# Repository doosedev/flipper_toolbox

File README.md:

<!-- Improved compatibility of back to top link: See: https://github.com/othneildrew/Best-README-Template/pull/73 -->

<!--
*** Thanks for checking out the Best-README-Template. If you have a suggestion
*** that would make this better, please fork the repo and create a pull request
*** or simply open an issue with the tag "enhancement".
*** Don't forget to give the project a star!
*** Thanks again! Now go create something AMAZING! :D
-->

<!-- PROJECT SHIELDS -->
<!--
*** I'm using markdown "reference style" links for readability.
*** Reference links are enclosed in brackets [ ] instead of parentheses ( ).
*** See the bottom of this document for the declaration of the reference variables
*** for contributors-url, forks-url, etc. This is an optional, concise syntax you may use.
*** https://www.markdownguide.org/basic-syntax/#reference-style-links
-->

<!-- PROJECT LOGO -->
<div align="center">
  <a href="https://github.com/doosedev/flipper_toolbox">
    <picture>
      <source media="(prefers-color-scheme: dark)" srcset="/.github/assets/banner_dark.png">
      <source media="(prefers-color-scheme: light)" srcset="/.github/assets/banner_light.png">
      
    </picture>
  </a>

  <br/>

  [![Contributors][contributors-shield]][contributors-url]
  [![Forks][forks-shield]][forks-url]
  [![Stargazers][stars-shield]][stars-url]<br/>
  [![Issues][issues-shield]][issues-url]
  [![MIT License][license-shield]][license-url]
  [![LinkedIn][linkedin-shield]][linkedin-url]

  <h3 align="center">Flipper Toolbox</h3>

  <p align="center">
    A collection of useful expansion boards for Flipper Zero
    <br/>
    <a href="https://github.com/doosedev/flipper_toolbox/issues">Report Bug</a>
    ·
    <a href="https://github.com/doosedev/flipper_toolbox/issues">Request Feature</a>
  </p>
</div>

<!-- MARKDOWN LINKS & IMAGES -->
<!-- https://www.markdownguide.org/basic-syntax/#reference-style-links -->
[contributors-shield]: https://img.shields.io/github/contributors/doosedev/flipper_toolbox.svg?style=for-the-badge
[contributors-url]: https://github.com/doosedev/flipper_toolbox/graphs/contributors
[forks-shield]: https://img.shields.io/github/forks/doosedev/flipper_toolbox.svg?style=for-the-badge
[forks-url]: https://github.com/doosedev/flipper_toolbox/network/members
[stars-shield]: https://img.shields.io/github/stars/doosedev/flipper_toolbox.svg?style=for-the-badge
[stars-url]: https://github.com/doosedev/flipper_toolbox/stargazers
[issues-shield]: https://img.shields.io/github/issues/doosedev/flipper_toolbox.svg?style=for-the-badge
[issues-url]: https://github.com/doosedev/flipper_toolbox/issues
[license-shield]: https://img.shields.io/github/license/doosedev/flipper_toolbox.svg?style=for-the-badge
[license-url]: https://github.com/doosedev/flipper_toolbox/blob/master/LICENSE.txt
[linkedin-shield]: https://img.shields.io/badge/-LinkedIn-black.svg?style=for-the-badge&logo=linkedin&colorB=555
[linkedin-url]: https://linkedin.com/in/jordan-doose-381bb4161

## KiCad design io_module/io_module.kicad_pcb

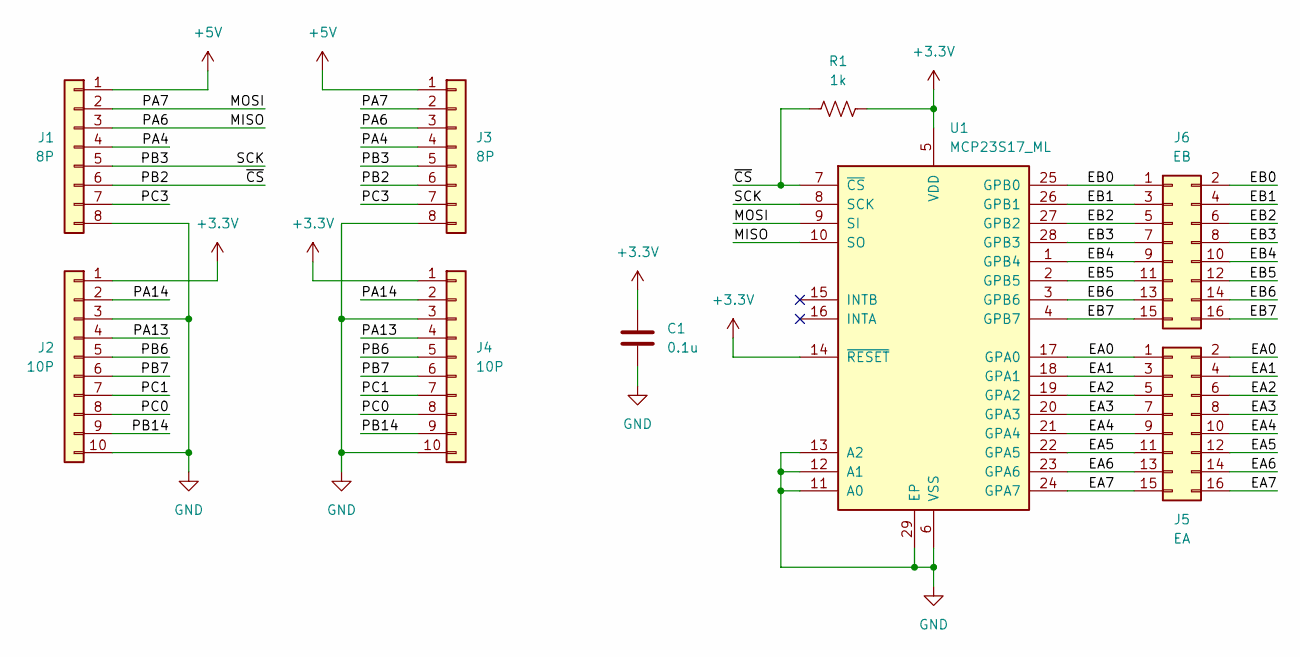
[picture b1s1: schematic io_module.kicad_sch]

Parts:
C1: 0.1u; C_0603_1608Metric_Pad1.08x0.95mm_HandSolder
J1: 8P; PinHeader_1x08_P2.54mm_Horizontal
J2: 10P; PinHeader_1x10_P2.54mm_Horizontal
J3: 8P; PinHeader_1x08_P2.54mm_Vertical
J4: 10P; PinHeader_1x10_P2.54mm_Vertical
J5: EA; PinHeader_2x08_P2.54mm_Vertical
J6: EB; PinHeader_2x08_P2.54mm_Vertical
R1: 1k; R_0603_1608Metric_Pad0.98x0.95mm_HandSolder
U1: MCP23S17_ML; QFN-28-1EP_6x6mm_P0.65mm_EP4.25x4.25mm

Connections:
+3.3V: C1.1, J2.1, J4.1, R1.2, U1.5 (VDD), U1.14 (~RESET)
+5V: J1.1, J3.1
/EA0: J5.1, J5.2, U1.17 (GPA0)
/EA1: J5.3, J5.4, U1.18 (GPA1)
/EA2: J5.5, J5.6, U1.19 (GPA2)
/EA3: J5.7, J5.8, U1.20 (GPA3)
/EA4: J5.9, J5.10, U1.21 (GPA4)
/EA5: J5.11, J5.12, U1.22 (GPA5)
/EA6: J5.13, J5.14, U1.23 (GPA6)
/EA7: J5.15, J5.16, U1.24 (GPA7)
/EB0: J6.1, J6.2, U1.25 (GPB0)
/EB1: J6.3, J6.4, U1.26 (GPB1)
/EB2: J6.5, J6.6, U1.27 (GPB2)
/EB3: J6.7, J6.8, U1.28 (GPB3)
/EB4: J6.9, J6.10, U1.1 (GPB4)
/EB5: J6.11, J6.12, U1.2 (GPB5)
/EB6: J6.13, J6.14, U1.3 (GPB6)
/EB7: J6.15, J6.16, U1.4 (GPB7)
/MISO: J1.3, J3.3, U1.10 (SO)
/MOSI: J1.2, J3.2, U1.9 (SI)
/PA4: J1.4, J3.4
/PA13: J2.4, J4.4
/PA14: J2.2, J4.2
/PB2: J1.6, J3.6, R1.1, U1.7 (~CS)
/PB3: J1.5, J3.5, U1.8 (SCK)
/PB6: J2.5, J4.5
/PB7: J2.6, J4.6
/PB14: J2.9, J4.9
/PC0: J2.8, J4.8
/PC1: J2.7, J4.7
/PC3: J1.7, J3.7
GND: C1.2, J1.8, J2.3, J2.10, J3.8, J4.3, J4.10, U1.6 (VSS), U1.11 (A0), U1.12 (A1), U1.13 (A2), U1.29 (EP)

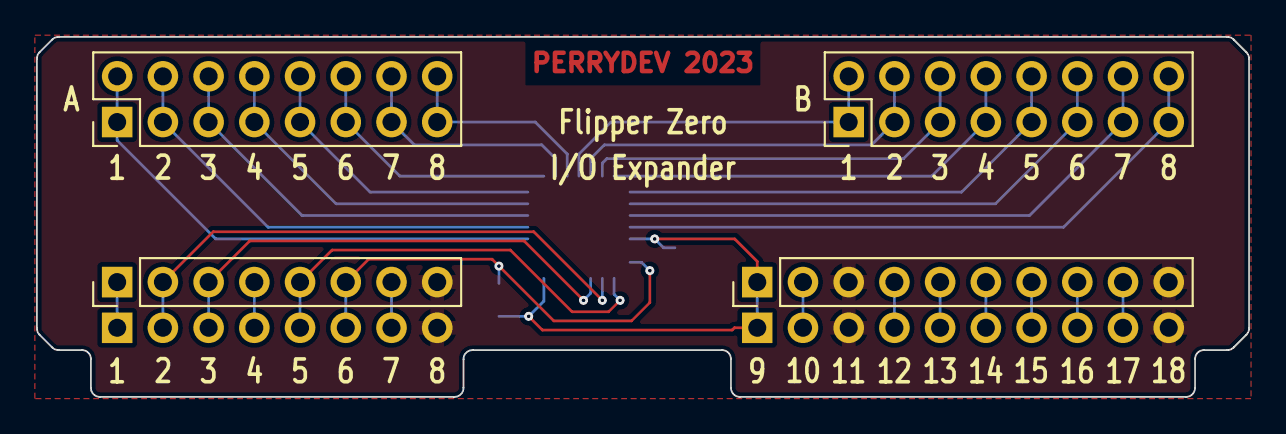
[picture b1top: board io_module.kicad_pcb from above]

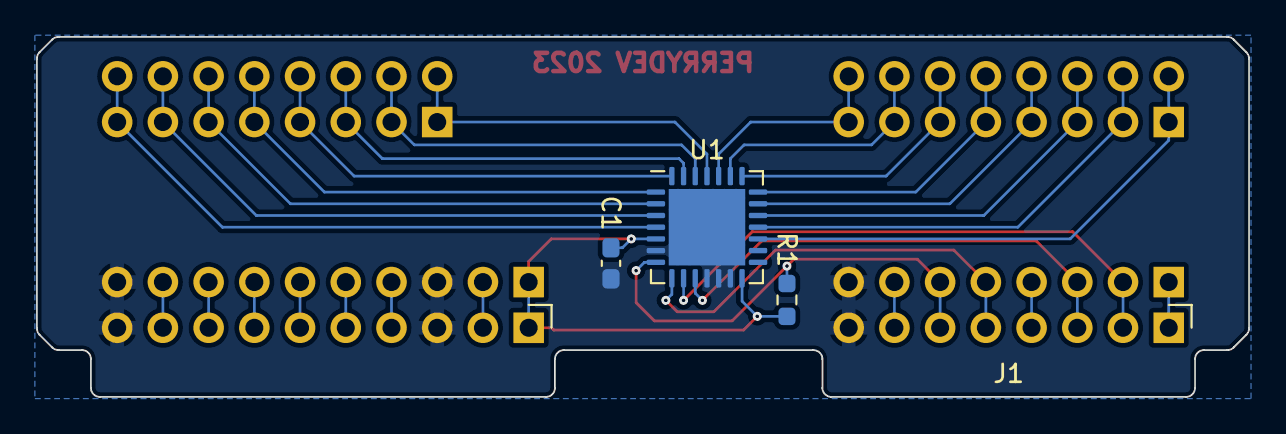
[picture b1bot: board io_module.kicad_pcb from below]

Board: 2 copper layers, 67.3 x 20.0 mm, 9 parts (5 on the bottom side), 32 nets.

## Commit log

2023-01-19 Initialize README
2023-01-19 swapped light/dark theme whoops
2023-01-19 center banner
2023-01-19 update .gitignore to ignore backups
2023-01-19 blank module design files
2023-01-20 relative lib path
2023-01-21 io module r1
2023-01-22 io module silkscreen
2023-01-22 io expansion board r2
